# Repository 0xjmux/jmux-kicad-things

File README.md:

# jmux-kicad-things

A place for my kicad symbols, footprints, template files and other miscellanea.

This is best used with a clean Kicad installation. 

Some symbols/footprints in here are imported from easyeda using [easyeda2kicad](https://hackaday.com/2023/08/08/easyeda2kicad-never-draw-a-footprint-again/), others are drawn by me for specific components I commonly use, and others are of my own creation. 

I try to keep this repo clean from included libraries, but mistakes happen. If you notice something, please open an issue. 

A lot of my designs also incorporate things from the following libraries:
* [kicad-tag-connect](https://github.com/nawotech/kicad-tag-connect) by nawotech
* [SOICbite](https://github.com/SimonMerrett/SOICbite) by SimonMerrett
* The Espressif KiCad Library (installed via Kicad)

> [!NOTE]
> As of Feb 2024 the full functionality of the `setup-kicad-things.sh` script has not been tested from-scratch, since my environment is already configured. When I get the chance to test it, this warning will be removed. Until then, use with caution.

###### Setup
To set up templates, libraries, and other files, run `setup-kicad-things.sh`. This script sets up symlinks from `~/.local/share/kicad/7.0/` to the directories in this repo, and moves any existing files into subdirectories under `old_kicad_conf/`. These files can then be manually moved into their corresponding directories in the repo.

This makes setup easy, and prevents excessive modification of the kicad local configuration directory. To remove this repo, just delete the symlinks. 

### Repo Highlights
* SOICBite UART and JTAG connector symbols for custom boards
<p align="center">
<br>
Example of the SOICBite symbol in use, from my iot_pwm_leddriver project. 
</p>

* Reversible UART bridge, which lets you easily swap your TX/RX in case you mess it up on a prototype. 
    * To use, just include the symbol and footprint in your design and wire it up as shown. If there's an issue, cut the solderjumper bridge and solder 0805 0Ω resistors vertically. 
    * This is fine for UART, but for signals of higher frequencies you might run into issues because of impedance mismatch and the number of sharp edges present. 
<p align="center">
<br>
Layout example for the UART bridge
</p>

* Templates for the ESP8266 and ESP32-SOLO, set up with my default parts (most of which are from the JLCPCB Basic parts library)
<p align="center">
<br>
Template page and description for my ESP32-Solo template
</p>

* `Breadboard-Proto` symbol library, quick symbols for breadboard project protyping. 

### Contents
* `footprints` contains footprints for my commonly used components along with custom ones
* `my_schematics` - schematics I commonly use in my designs
* `symbols` - Schematic symbols
* `templates` - My templates for automatically setting up projects
* `setup-kicad-things.sh` - script to set up repo, see [#Setup](#Setup) above.

#### Structure

```
├── README.md
├── setup-kicad-things.sh
├── footprints
│   ├── jmux-footprints.pretty
│   └── packages3d
├── my_schematics
│   └── Power_and_board.kicad_sch
├── old_kicad_confs/
├── symbols
│   ├── Breadboard-Proto.kicad_sym
│   └── jmux-kicadlib.kicad_sym
└── templates
    ├── esp32-s2-solo-template
    └── esp8266-template
    
```

## Other
### easyeda2kicad shortcut from my .zshrc
In case anyone else finds it useful. Just provide the LCSC id and run it from the project folder, and as long as `./projectlib/` is created everything works nice and smooth. 
```sh
# easyeda2kicad shortcut just requiring the LCSC id, designed to be run from project folder
alias e2kicad="easyeda2kicad --output ./projectlib/projectlib --full --lcsc_id "
```

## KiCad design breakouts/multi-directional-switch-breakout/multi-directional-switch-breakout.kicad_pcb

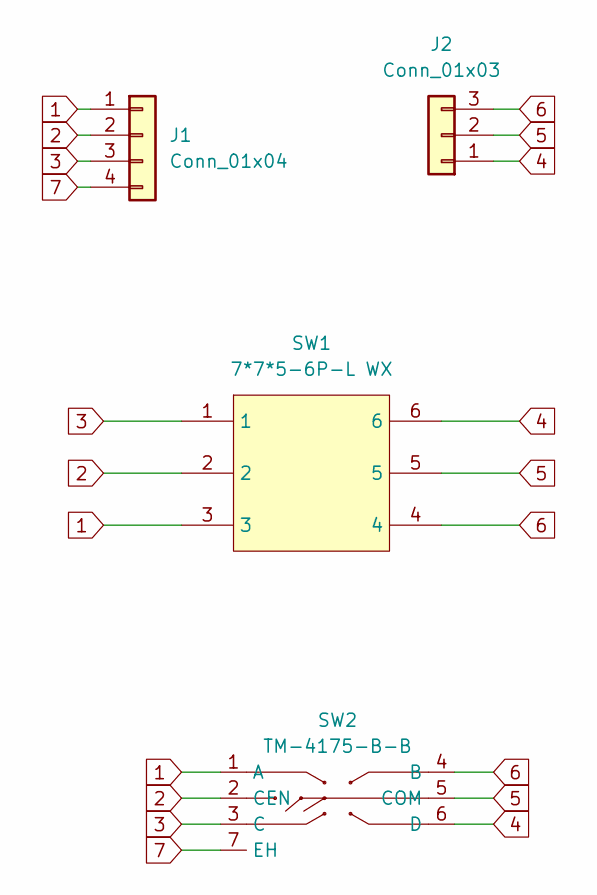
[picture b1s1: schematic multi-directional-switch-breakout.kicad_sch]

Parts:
J1: Conn_01x04; PinHeader_1x04_P2.54mm_Vertical
J2: Conn_01x03; PinHeader_1x03_P2.54mm_Vertical
SW1: 7*7*5-6P-L WX; SW-SMD_8P-L7.0-W7.0-P1.40-LS7.4-TL; LCSC Part C2858287
SW2: TM-4175-B-B; SW-SMD_TM-4175-B-X; LCSC Part C465996

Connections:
1: J1.1, SW1.3, SW2.1 (A)
2: J1.2, SW1.2, SW2.2 (CEN)
3: J1.3, SW1.1, SW2.3 (C)
4: J2.1, SW1.6, SW2.6 (D)
5: J2.2, SW1.5, SW2.5 (COM)
6: J2.3, SW1.4, SW2.4 (B)
7: J1.4, SW2.7 (EH)

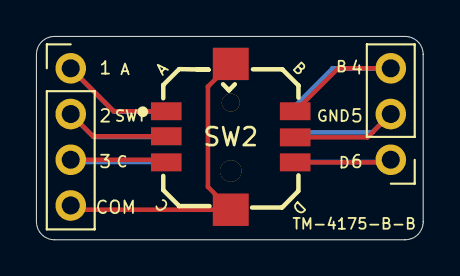
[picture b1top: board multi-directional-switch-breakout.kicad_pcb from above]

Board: 2 copper layers, 21.5 x 11.3 mm, 4 parts (1 on the bottom side), 7 nets.

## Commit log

2023-12-23 first commit and my existing files
2024-01-08 Updates and added new footprints
2024-01-12 fixes to script and correctly named template dir
2024-01-27 esp32-s2 template and tag-conn symbols
2024-02-05 updated readme and several new additions to sym and fp libs
2024-02-06 readme updates to take repo public
2024-02-06 readme update warning
2024-02-06 readme warning for reversible uart
2024-02-06 Update README.md seplling
2024-02-06 added e2kicad shortcut to readme
2024-02-06 update after merge
2024-03-22 new footprints, including new version of my standard usb C GT7010
2024-03-22 moved pads on fixed USB GT7010 to hopefully fix DRC issues during layout
2024-06-16 helix antenna, rylr998, ILI9341 display
2024-07-20 add ILI9341 footprint and multi-dir swt breakout
